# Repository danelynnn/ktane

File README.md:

# ktane

keep talkin and nobody goes poof :D

this is a physical recreation of the... _briefcase_, from KEEP TALKING AND NOBODY \<REDACTED\>. the intention of this project is to be as faithful as possible to the original, so some modules might not be included or otherwise altered so that they can exist within the fabric of reality :]

# gameplay loop

as reality cannot be procedurally generated, and is hence often disappointing, the briefcase must be set up at a designated time before the game is considered "active", where every physical element can be assembled manually.

as such, the briefcase will have the following states:

```
enum Phase {
  SETUP, ACTIVE, SOLVED
};
```

1. setup (if applicable):  
   puzzle is inactive, time is frozen at starting time (e.g. 5:00)  
   modules can be inserted or disconnected  
   modules cannot cause strikes or be completed

2. active:
   puzzle is active, time will start ticking down, and modules can be completed/cause mistakes

3. solved (win/loss):
   puzzle is inactive, time is at 0:00  
   modules should not be connected or disconnected at this time  
   modules cannot cause strikes or be completed

# modules

as the original game is grouped into modules, it'd be an absolute shame not to engineer the recreation as modular, as each physical "module" can roughly correspond to one virtual module.

## generic module implementation

each of these modules will be designed as a standalone ATMega328p (IC from an Arduino R3), as this is a lot more cost-effective than dedicating an entire dev board to a module.

as the modules must stay in sync and send/receive information, they must be connected through communication. we're using a simple 2-wire I<sup>2</sup>C communication bus (for details, see "Communication")

all modules will have four pinouts to connect to a bus, aside from the exposed interfaces needed for the module:

- 5v (red)
- gnd (black)
- scl (white)
- sda (yellow)

further circuit schematics can be found in the `kicad/` folder.

## controller "module"

this isn't an actual module, but it has the same footprint and effectively acts as a normal module, so we're counting it here. this is the designated main hub for all of the briefcase's unique properties, including:

- battery count
- indicators
- serial number
- strikes
- timer

this controller will also include a handful of interactive elements, such as a speaker for sound effects and buttons to configure and advance state.

## wires module (finally, the good stuff)

during setup phase, this module will accept any number of pin connections between the 6 left and 6 right terminals. these connections must be made with custom wires with a resistance representing their colour, as follows:

- yellow: 100 &#937;
- red: 220 &#937;
- blue: 470 &#937;
- black: 680 &#937;
- white: 1k &#937;

once setup phase is complete, the module will commit the final configuration of the wires as the "starting state", and any disconnections will cause either a strike or a completion.

any CONNECTIONS... i mean, idk man don't do that lol

# communication

communication across the puzzle is handled through an I<sup>2</sup>C multi-master (different addresses can choose to initiate communication) bus. currently, there is no plan to implement arbitration, so a simple protocol must be created to prevent crosstalk. the general idea is that for any given "state change" event (e.g. user interacting with a module, module/controller connecting, needy module reactivating), only one address should be initiating communication, though this can include any number or combination of send/receives.

## controller

always on address 8

### possible initiations

- request state from module
- send reset signal to module
- send activate signal to module

## module

allocated 56 addresses, could be between 9-64  
there are 14 total modules, but addresses must be unique, so each module type can assign as one of 4 addresses:

- 9-12: wires
- 13-16: button
- 17-20: keypad
- 21-24: simon says
- 25-28: who's on first
- 29-32: memory
- 33-36: morse code
- 37-40: complicated wires
- 41-44: wire sequences(??)
- 45-48: maze
- 49-52: password
- 53-56: gas
- 57-60: capacitor
- 61-64: knob

### possible initiations

- request data from controller
- send status to controller (-1/255 for "caused strike")

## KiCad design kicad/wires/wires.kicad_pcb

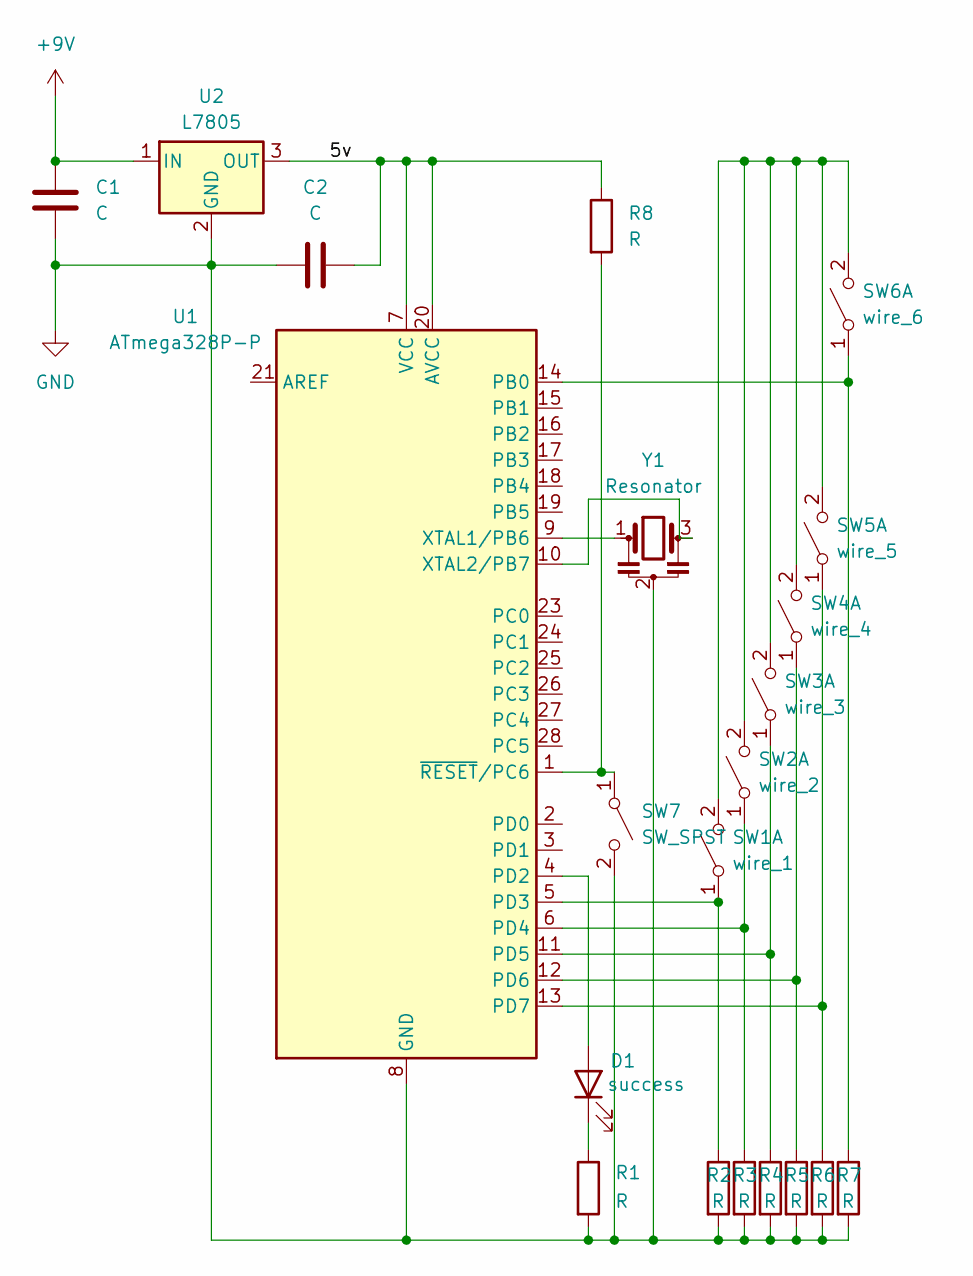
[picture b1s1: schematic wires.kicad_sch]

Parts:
C1, C2: C; CP_Radial_D5.0mm_P2.50mm
D1: success; LED_D8.0mm
R1, R2, R3, R4, R5, R6, R7, R8: R; R_Axial_DIN0207_L6.3mm_D2.5mm_P10.16mm_Horizontal
SW1: wire_1; SW_DIP_SPSTx01_Slide_6.7x4.1mm_W8.61mm_P2.54mm_LowProfile
SW2: wire_2; SW_DIP_SPSTx01_Slide_6.7x4.1mm_W8.61mm_P2.54mm_LowProfile
SW3: wire_3; SW_DIP_SPSTx01_Slide_6.7x4.1mm_W8.61mm_P2.54mm_LowProfile
SW4: wire_4; SW_DIP_SPSTx01_Slide_6.7x4.1mm_W8.61mm_P2.54mm_LowProfile
SW5: wire_5; SW_DIP_SPSTx01_Slide_6.7x4.1mm_W8.61mm_P2.54mm_LowProfile
SW6: wire_6; SW_DIP_SPSTx01_Slide_6.7x4.1mm_W8.61mm_P2.54mm_LowProfile
SW7: SW_SPST; SW_SPST_TS-1088-xR025
U1: ATmega328P-P; DIP-28_W7.62mm
U2: L7805; TO-220-3_Horizontal_TabDown
Y1: Resonator; Resonator-3Pin_W10.0mm_H5.0mm

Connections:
+9V: C1.1, U2.1 (IN)
/5v: C2.1, R8.1, U1.7 (VCC), U1.20 (AVCC), U2.3 (OUT)
GND: C1.2, C2.2, R1.2, R2.2, R3.2, R4.2, R5.2, R6.2, R7.2, SW7.2 (B), U1.8 (GND), U1.22 (GND), U2.2 (GND), Y1.2
unnamed: D1.2 (A), U1.4 (PD2)
unnamed: D1.1 (K), R1.1
unnamed: R2.1, SW1.1 (A), U1.5 (PD3)
unnamed: SW1.2 (B), SW2.2 (B), SW3.2 (B), SW4.2 (B), SW5.2 (B), SW6.2 (B)
unnamed: R3.1, SW2.1 (A), U1.6 (PD4)
unnamed: R4.1, SW3.1 (A), U1.11 (PD5)
unnamed: R5.1, SW4.1 (A), U1.12 (PD6)
unnamed: R6.1, SW5.1 (A), U1.13 (PD7)
unnamed: R7.1, SW6.1 (A), U1.14 (PB0)
unnamed: R8.2, SW7.1 (A), U1.1 (~RESET/PC6)
unnamed: U1.9 (XTAL1/PB6), Y1.1
unnamed: U1.10 (XTAL2/PB7), Y1.3

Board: 2 copper layers, 21 parts (0 on the bottom side), 15 nets, no tracks yet.

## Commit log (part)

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2024-12-09 the first day
2024-12-09 RULES ARE DONE (and like partially tested?)
2024-12-10 MODULE LOGIC IS COMPLETE (with a success pin)
2024-12-10 organised wires & file structure
2024-12-10 blinky circuit is alive
2024-12-11 holy shit simon says module is just done, literally perfectly
2024-12-12 fixed problem with timer because the start variable i was using to determine the start of the color cycle was an int and that fucked up math woo
2024-12-12 reset phase and added layout photo
2025-08-01 added old processing app into the fray
2026-06-04 COMMUNICATION HAS BEEN CREATED!!!!
2026-06-23 COMMUNICATION MADE FLEXIBLE (modules can now join at any order with no desyncing)
